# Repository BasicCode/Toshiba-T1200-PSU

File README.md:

# Toshiba-T1200-PSU

A replacement power supply design for the Toshiba T1200 laptop computer from 1987. The Toshiba T1xxx series are notorious for power supply falures, and the power supply design is complex for the era. While the complicated design did allow for some innovative new power management features for the time, it also allowed for a myriad of annoying failure modes. I say this only because I have not implemented most of the auxiliary features here, but they may be desirable in the future.<br />
  
This is a drop-in replacement board which has the bare necessities to allow the machine to boot. It does not support the "advanced" features like HDD power management, battery charging, or even battery power supply. It provides two +5V rails, a +12V rail for the HDD, a -22V rail for the LCD, and also a -9V rail for the RS232 modem. Most of these are provided by off-the-shelf modules, however some parts had to be designed specifically for this purpose. The CPU data communication lines are also broken out to a header for anybody who would like to go down that rabbit hole; let me know how you go.
  
**NOTE:** While I have tried to design a safe system, and tested it using my own personal device as well as relevant test equipment, **I am only a hobbyist** and I strongly encourage you to make your own assessment of the quality of this device.
  
* [JLCPCB Project](https://oshwlab.com/tommy_tom2000/toshiba-t1200-power-supply-v1-3)
* [Buy on Tindie](https://www.tindie.com/products/basiccode/toshiba-t1200-power-supply/)

## Getting Started
The board is designed to be manufactured by JLCPCB using parts from LCSC. The full project is free to use and modify, and available [here](https://oshwlab.com/tommy_tom2000/toshiba-t1200-power-supply-v1-3). The Gerber and BoM files are provided here for those who do not want to use JLCPCB. The previous version of this project was more friendly for hand-soldering is also still available in [past commits](https://github.com/BasicCode/Toshiba-T1200-PSU/commit/b5f09ac5c124c712909910e9a37de9bca65d9860).

Some traces of power rail noise are included in the *images* directory. Ripple for the -22V and -9V rails were below the noise floor of my work bench and so have not been included.

## TODO and Errors
* Create a video or page to document the install process.
* 300mV ripple on the 12V rail under load, and a -1V spike when full load is applied. A clamping diode might be useful in a future revision.

## Thanks and References
Thanks to these forums for helping sole so many problems:
* https://forum.vcfed.org/index.php?threads/toshiba-t1200-internal-power-supply-issues.72126/
* https://forum.vcfed.org/index.php?threads/toshiba-t1200-psu-pinout.1216344/
* http://www.minuszerodegrees.net/manuals/Toshiba/Other/Toshiba%20T1200%20-%20Maintenance%20Manual.pdf

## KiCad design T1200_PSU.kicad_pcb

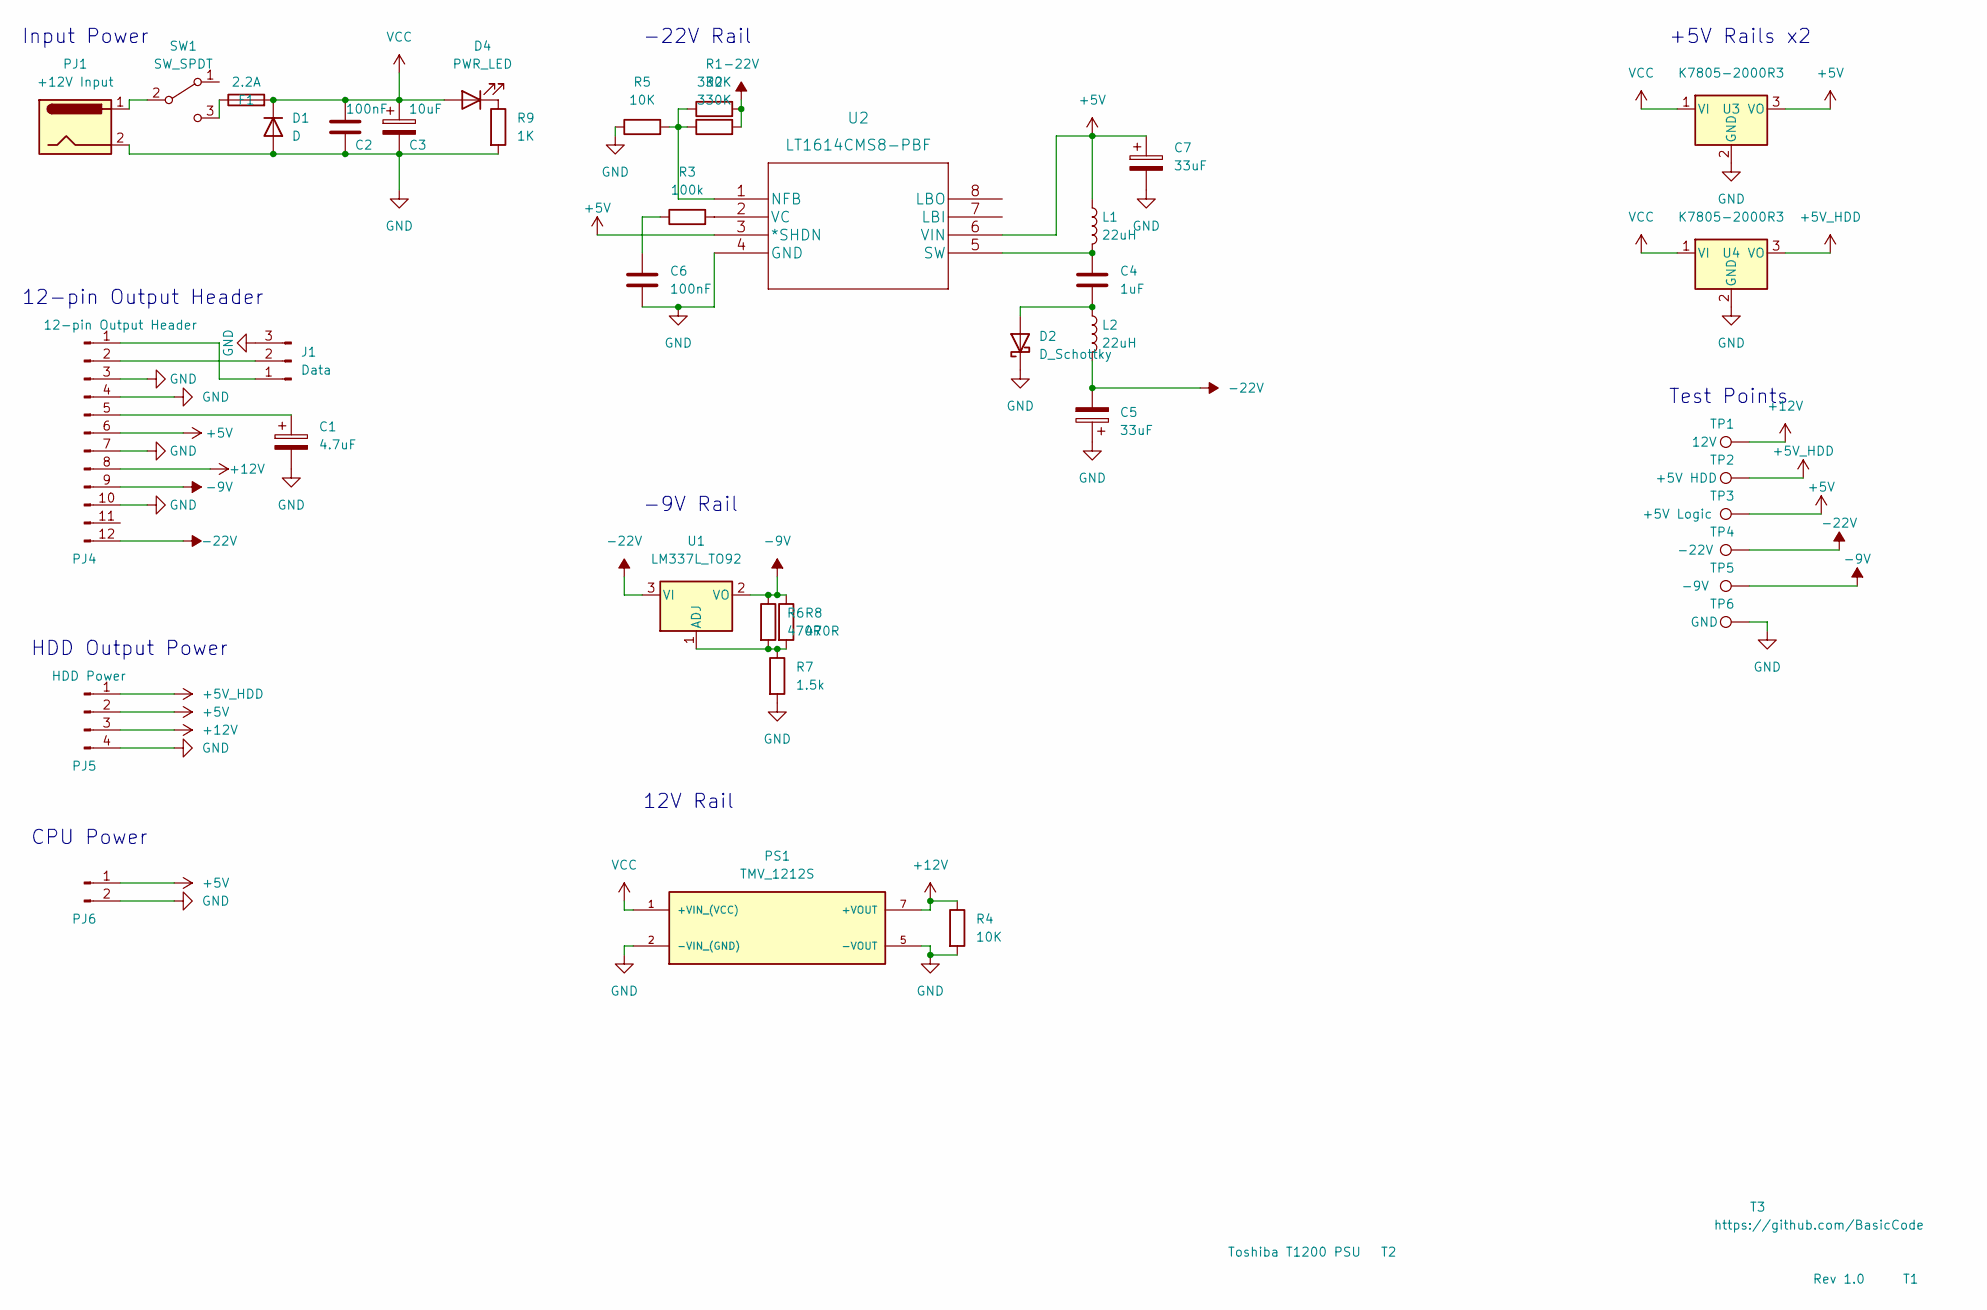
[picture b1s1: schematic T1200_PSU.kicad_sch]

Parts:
C1: 4.7uF; CP_Radial_D4.0mm_P2.00mm
C2, C6: 100nF; C_0805_2012Metric
C3: 10uF; CP_Radial_D4.0mm_P2.00mm
C4: 1uF; C_1206_3216Metric
C5, C7: 33uF; CP_Radial_D5.0mm_P2.50mm
D1: D; D_1206_3216Metric
D2: D_Schottky; D_0805_2012Metric_Pad1.15x1.40mm_HandSolder
D4: PWR_LED; LED_D5.0mm
F1: 2.2A; Fuse_1210_3225Metric
J1: Data; PinHeader_1x03_P2.54mm_Vertical
L1, L2: 22uH; L_5.3x5.0_H3
PJ1: +12V Input; BarrelJack_Horizontal
PJ4: 12-pin Output Header; PinHeader_1x12_P2.00mm_Vertical
PJ5: HDD Power; PinHeader_1x04_P2.54mm_Vertical
PJ6: PinHeader_1x02_P2.54mm_Vertical
PS1: TMV_1212S; CONV_TMV_1212S; PARTREV March 26, 2020
R1, R2: 330K; R_1206_3216Metric
R3: 100k; R_1206_3216Metric
R4, R5: 10K; R_1206_3216Metric
R6, R8: 470R; R_1206_3216Metric
R7: 1.5k; R_1206_3216Metric
R9: 1K; R_1206_3216Metric
SW1: SW_SPDT; switch
T1: Rev 1.0; text_only
T2: Toshiba T1200 PSU; text_only
T3: https://github.com/BasicCode; text_only
TP1: 12V; TestPoint_Pad_D1.5mm
TP2: +5V HDD; TestPoint_Pad_D1.5mm
TP3: +5V Logic; TestPoint_Pad_D1.5mm
TP4: -22V; TestPoint_Pad_D1.5mm
TP5: -9V; TestPoint_Pad_D1.5mm
TP6: GND; TestPoint_Pad_D1.5mm
U1: LM337L_TO92; TO-92_Inline
U2: LT1614CMS8-PBF; SSOP-8_3.9x5.05mm_P1.27mm
U3, U4: K7805-2000R3; TO-220-3_Vertical

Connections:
+5V: C7.1, L1.1, PJ4.6, PJ5.2, PJ6.1, TP3.1, U2.3 (*SHDN), U2.6 (VIN), U3.3 (VO)
+5V_HDD: PJ5.1, TP2.1, U4.3 (VO)
+12V: PJ4.8, PJ5.3, PS1.7 (+VOUT), R4.1, TP1.1
-9V: PJ4.9, R6.1, R8.1, TP5.1, U1.2 (VO)
-22V: C5.2, L2.2, PJ4.12, R1.2, R2.2, TP4.1, U1.3 (VI)
GND: C1.2, C2.2, C3.2, C5.1, C6.2, C7.2, D1.2 (A), D2.1 (K), J1.3, PJ1.2, PJ4.3, PJ4.4, PJ4.7, PJ4.10, PJ5.4, PJ6.2, PS1.2 (-VIN_(GND)), PS1.5 (-VOUT), R4.2, R5.1, R7.2, R9.2, TP6.1, U2.4 (GND), U3.2 (GND), U4.2 (GND)
unnamed: C1.1, PJ4.5
unnamed: C4.1, L1.2, U2.5 (SW)
unnamed: C4.2, D2.2 (A), L2.1
unnamed: C6.1, R3.1
unnamed: D4.1 (K), R9.1
unnamed: F1.1, SW1.3 (C)
unnamed: J1.1, PJ4.1
unnamed: J1.2, PJ4.2
unnamed: PJ1.1, SW1.2 (B)
unnamed: R1.1, R2.1, R5.2, U2.1 (NFB)
unnamed: R3.2, U2.2 (VC)
unnamed: R6.2, R7.1, R8.2, U1.1 (ADJ)
VCC: C2.1, C3.1, D1.1 (K), D4.2 (A), F1.2, PS1.1 (+VIN_(VCC)), U3.1 (VI), U4.1 (VI)

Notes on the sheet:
+5V Rails x2
-22V Rail
Test Points
HDD Output Power
CPU Power
Input Power
12-pin Output Header
12V Rail
-9V Rail

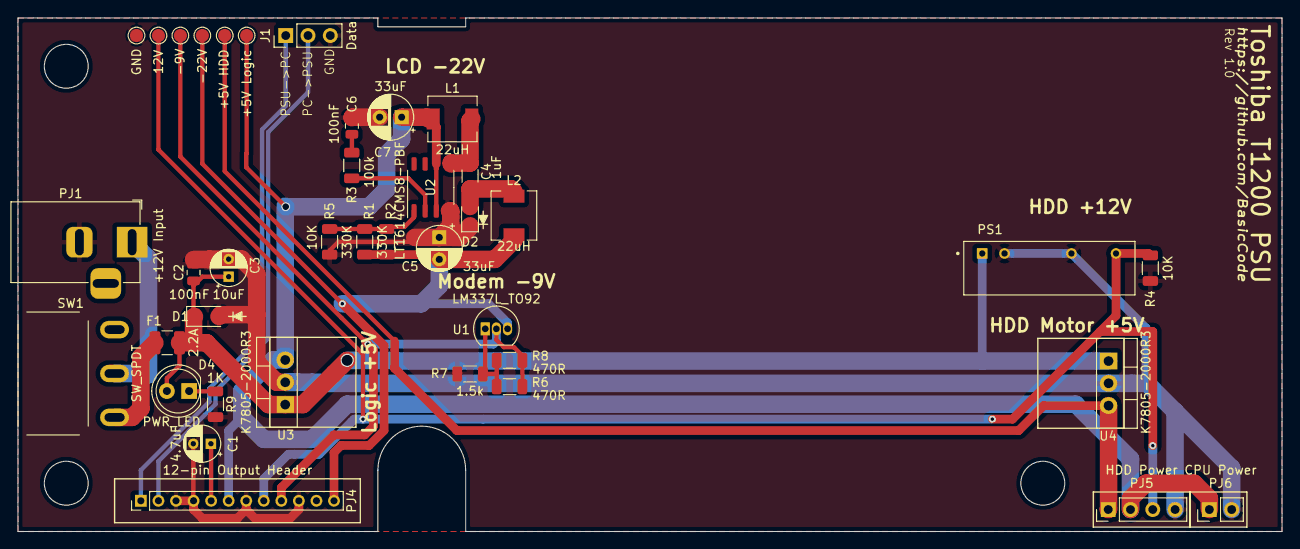
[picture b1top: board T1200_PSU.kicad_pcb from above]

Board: 2 copper layers, 144.0 x 58.5 mm, 42 parts (0 on the bottom side), 19 nets.

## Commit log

2022-04-13 add images
2022-04-13 try again with images
2022-04-13 add references
2022-04-24 revision 1.0
2022-04-26 update documentation
2022-05-07 clean up custom assets with absolute paths
2022-05-07 clean up gitignore file
2022-05-07 clean up old files
2022-08-02 added BOM file for DigiKey
2023-02-27 Add DigiKey Parts List
    Include a link to the component parts list on Digikey.
2024-04-10 Migrate to JLCPCB
2024-04-10 Complete re-design on JLCPCB
2024-04-10 fix typo, and bad ignore file.
2024-04-10 include schematic
2024-04-12 oops wrong link
2024-04-12 add purchase link
2024-05-02 include load characterisation
2024-10-18 Rev 1.3
2024-10-18 fix old link
